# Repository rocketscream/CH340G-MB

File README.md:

# WCH CH340G USB-Serial Adapter Board
WCH CH340G board is a cost effective USB-serial adapter with the ever familiar FTDI 6-pin female header which you can use with Arduino Pro or Pro Mini for both 3.3V and 5V version. The board supports both 5V and 3.3V IO voltage level through a slide switch. The board also has an on-board 3.3V LDO regulator to provide up to 250 mA of output current. The VCC pin on the 6-pin female header can be selectable to be either 5V or 3.3V. A green and red LED indicate TX & RX activity of the board. A resettable 0.5A fuse is included to provide protection to the USB port from over current. All other pins like RTS, DTR, DCD, RI, DSR, and CTS are made available for use on the side of the board.

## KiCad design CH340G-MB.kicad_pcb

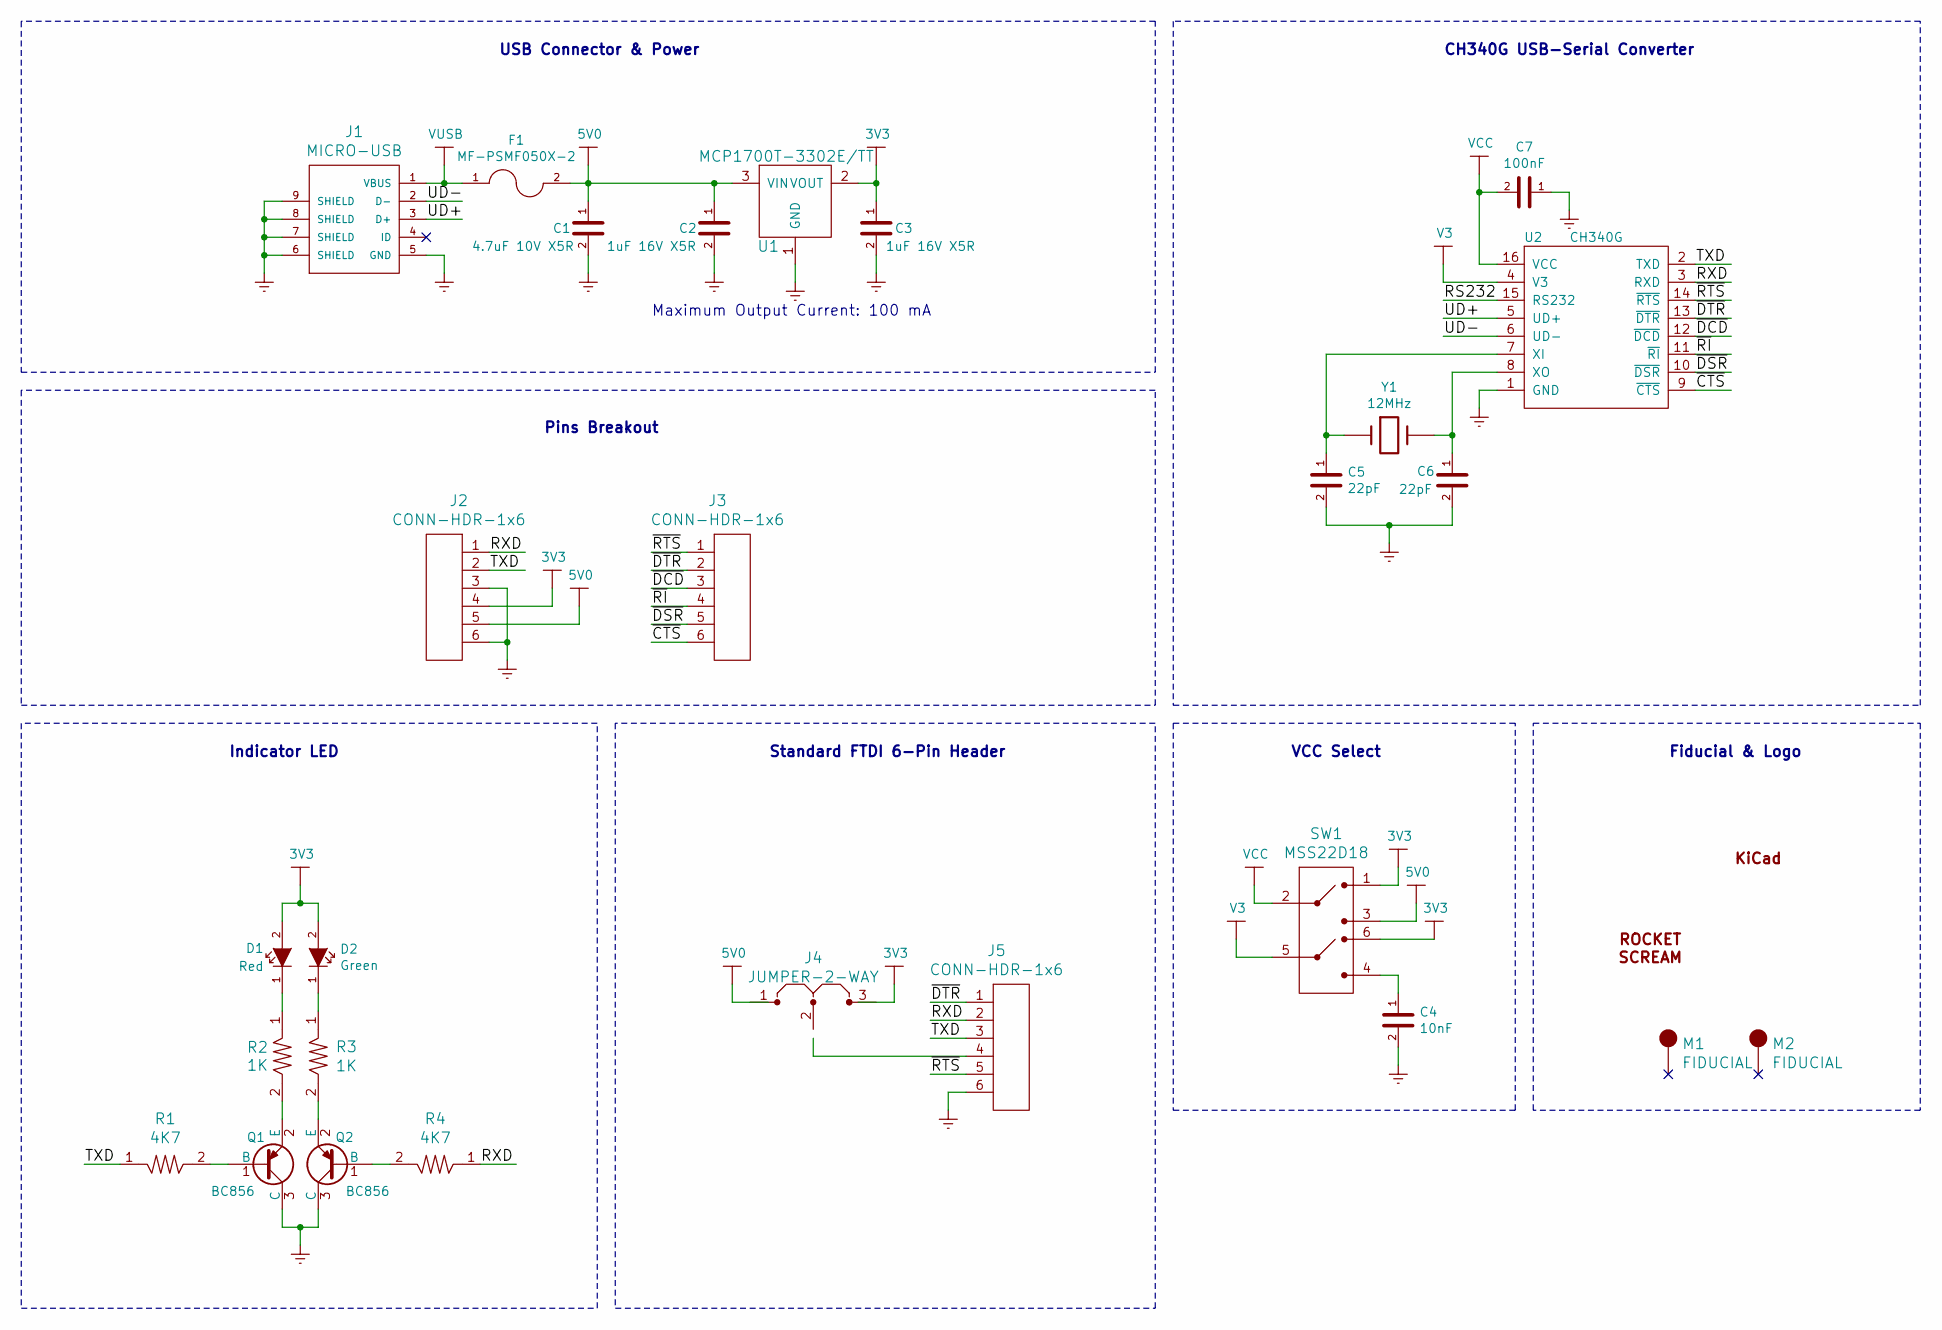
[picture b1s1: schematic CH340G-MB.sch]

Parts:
C1: 4.7uF 10V X5R; CAP-0603
C2, C3: 1uF 16V X5R; CAP-0603
C4: 10nF; CAP-0603
C5, C6: 22pF; CAP-0603
C7: 100nF; CAP-0603
D1: Red; LED-0603
D2: Green; LED-0603
F1: MF-PSMF050X-2; MF-PSMF020X
J1: MICRO-USB
J2, J3: CONN-HDR-1x6; HDR_1x6_Pitch2.54mm_WithoutSilk
J4: JUMPER-2-WAY; JUMPER-2-WAY-SMD
J5: CONN-HDR-1x6; RCP_1x6_Pitch2.54mm_RightAngle
LOGO1: LOGO-ROCKET-SCREAM; LOGO-ROCKET-SCREAM_Vertical_XSmall
LOGO2: LOGO-KICAD; LOGO-KICAD_XSmall
M1, M2: FIDUCIAL; FIDUCIAL-1MM
Q1, Q2: BC856; SOT-23
R1, R4: 4K7; RES-0603
R2, R3: 1K; RES-0603
SW1: MSS22D18
U1: MCP1700T-3302E/TT; SOT-23
U2: CH340G; SOP-16_150mil
Y1: 12MHz; ABM3

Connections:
3V3: C3.1, D1.2 (A), D2.2 (A), J2.4, J4.3, SW1.1, SW1.6, U1.2 (VOUT)
5V0: C1.1, C2.1, F1.2, J2.5, J4.1, SW1.3, U1.3 (VIN)
/RS232: U2.15 (RS232)
/RXD: J2.1, J5.2, R4.1, U2.3 (RXD)
/TXD: J2.2, J5.3, R1.1, U2.2 (TXD)
/UD+: J1.3 (D+), U2.5 (UD+)
/UD-: J1.2 (D-), U2.6 (UD-)
/~CTS: J3.6, U2.9 (~CTS)
/~DCD: J3.3, U2.12 (~DCD)
/~DSR: J3.5, U2.10 (~DSR)
/~DTR: J3.2, J5.1, U2.13 (~DTR)
/~RI: J3.4, U2.11 (~RI)
/~RTS: J3.1, J5.5, U2.14 (~RTS)
GND: C1.2, C2.2, C3.2, C4.2, C5.2, C6.2, C7.1, J1.5 (GND), J1.6 (SHIELD), J1.7 (SHIELD), J1.8 (SHIELD), J1.9 (SHIELD), J2.3, J2.6, J5.6, Q1.3 (C), Q2.3 (C), U1.1 (GND), U2.1 (GND)
unnamed: C4.1, SW1.4
unnamed: C5.1, U2.7 (XI), Y1.1
unnamed: C6.1, U2.8 (XO), Y1.2
unnamed: D1.1 (K), R2.1
unnamed: D2.1 (K), R3.1
unnamed: J4.2, J5.4
unnamed: Q1.1 (B), R1.2
unnamed: Q1.2 (E), R2.2
unnamed: Q2.1 (B), R4.2
unnamed: Q2.2 (E), R3.2
V3: SW1.5, U2.4 (V3)
VCC: C7.2, SW1.2, U2.16 (VCC)
VUSB: F1.1, J1.1 (VBUS)

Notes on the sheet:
Indicator LED
Standard FTDI 6-Pin Header
VCC Select
Fiducial & Logo
Pins Breakout
USB Connector & Power
Maximum Output Current: 100 mA
CH340G USB-Serial Converter

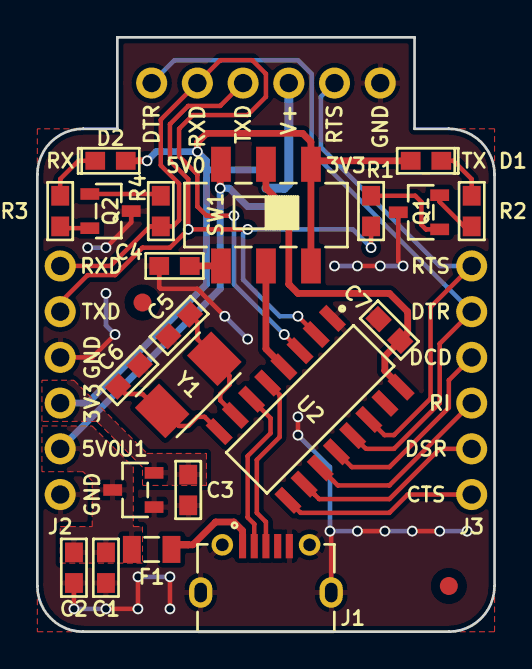
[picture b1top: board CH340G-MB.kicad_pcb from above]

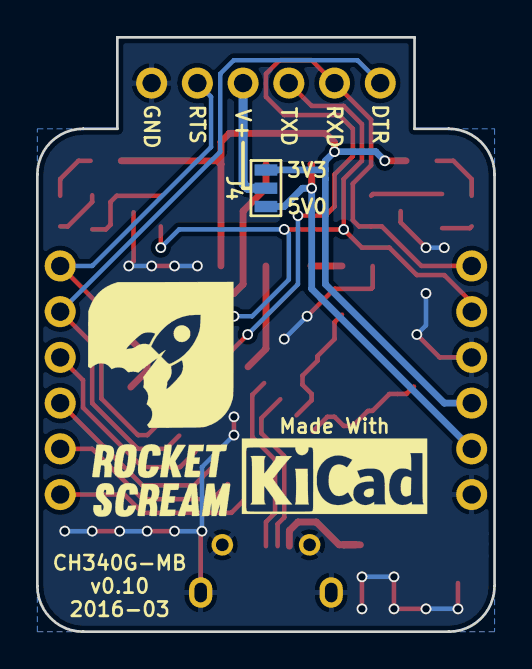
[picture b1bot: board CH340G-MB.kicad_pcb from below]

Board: 2 copper layers, 25.4 x 33.0 mm, 29 parts (3 on the bottom side), 26 nets.

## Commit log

2018-09-30 v1.00
